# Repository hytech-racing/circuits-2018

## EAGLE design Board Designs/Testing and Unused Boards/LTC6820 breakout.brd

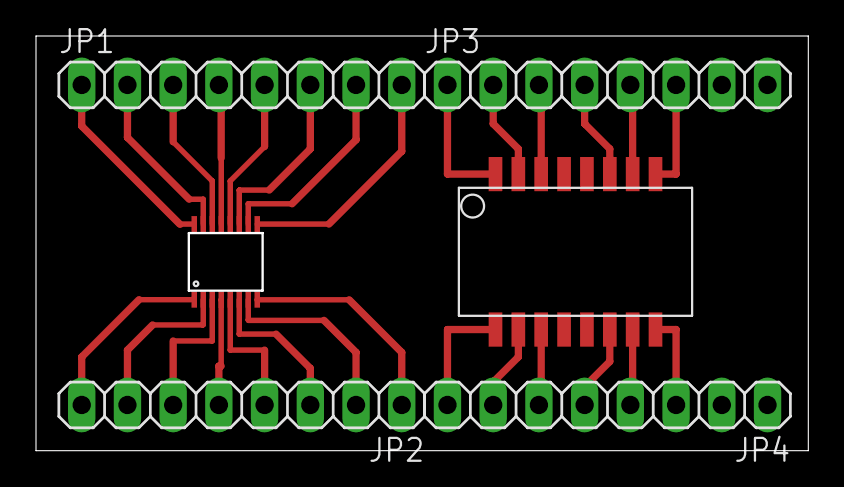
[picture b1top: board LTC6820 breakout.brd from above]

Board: 2 copper layers, 42.9 x 23.0 mm, 6 parts (0 on the bottom side), 23 nets.

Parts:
JP1, JP2, JP3, JP4: 1X08
U$1: LTC6820; MSOP-16
U$2: 749010013

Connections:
unnamed: JP2.1, U$1.8
unnamed: JP2.2, U$1.7
unnamed: JP2.3, U$1.6
unnamed: JP2.4, U$1.5
unnamed: JP2.5, U$1.4
unnamed: JP2.6, U$1.3
unnamed: JP2.7, U$1.2
unnamed: JP2.8, U$1.1
unnamed: JP1.1, U$1.16
unnamed: JP1.2, U$1.15
unnamed: JP1.3, U$1.14
unnamed: JP1.4, U$1.13
unnamed: JP1.5, U$1.12
unnamed: JP1.6, U$1.11
unnamed: JP1.7, U$1.10
unnamed: JP1.8, U$1.9
unnamed: JP4.8, U$2.16
unnamed: JP4.7, U$2.15
unnamed: JP4.6, U$2.14
unnamed: JP3.1, U$2.1
unnamed: JP3.2, U$2.2
unnamed: JP3.3, U$2.3
S$2: JP3.6, U$2.8

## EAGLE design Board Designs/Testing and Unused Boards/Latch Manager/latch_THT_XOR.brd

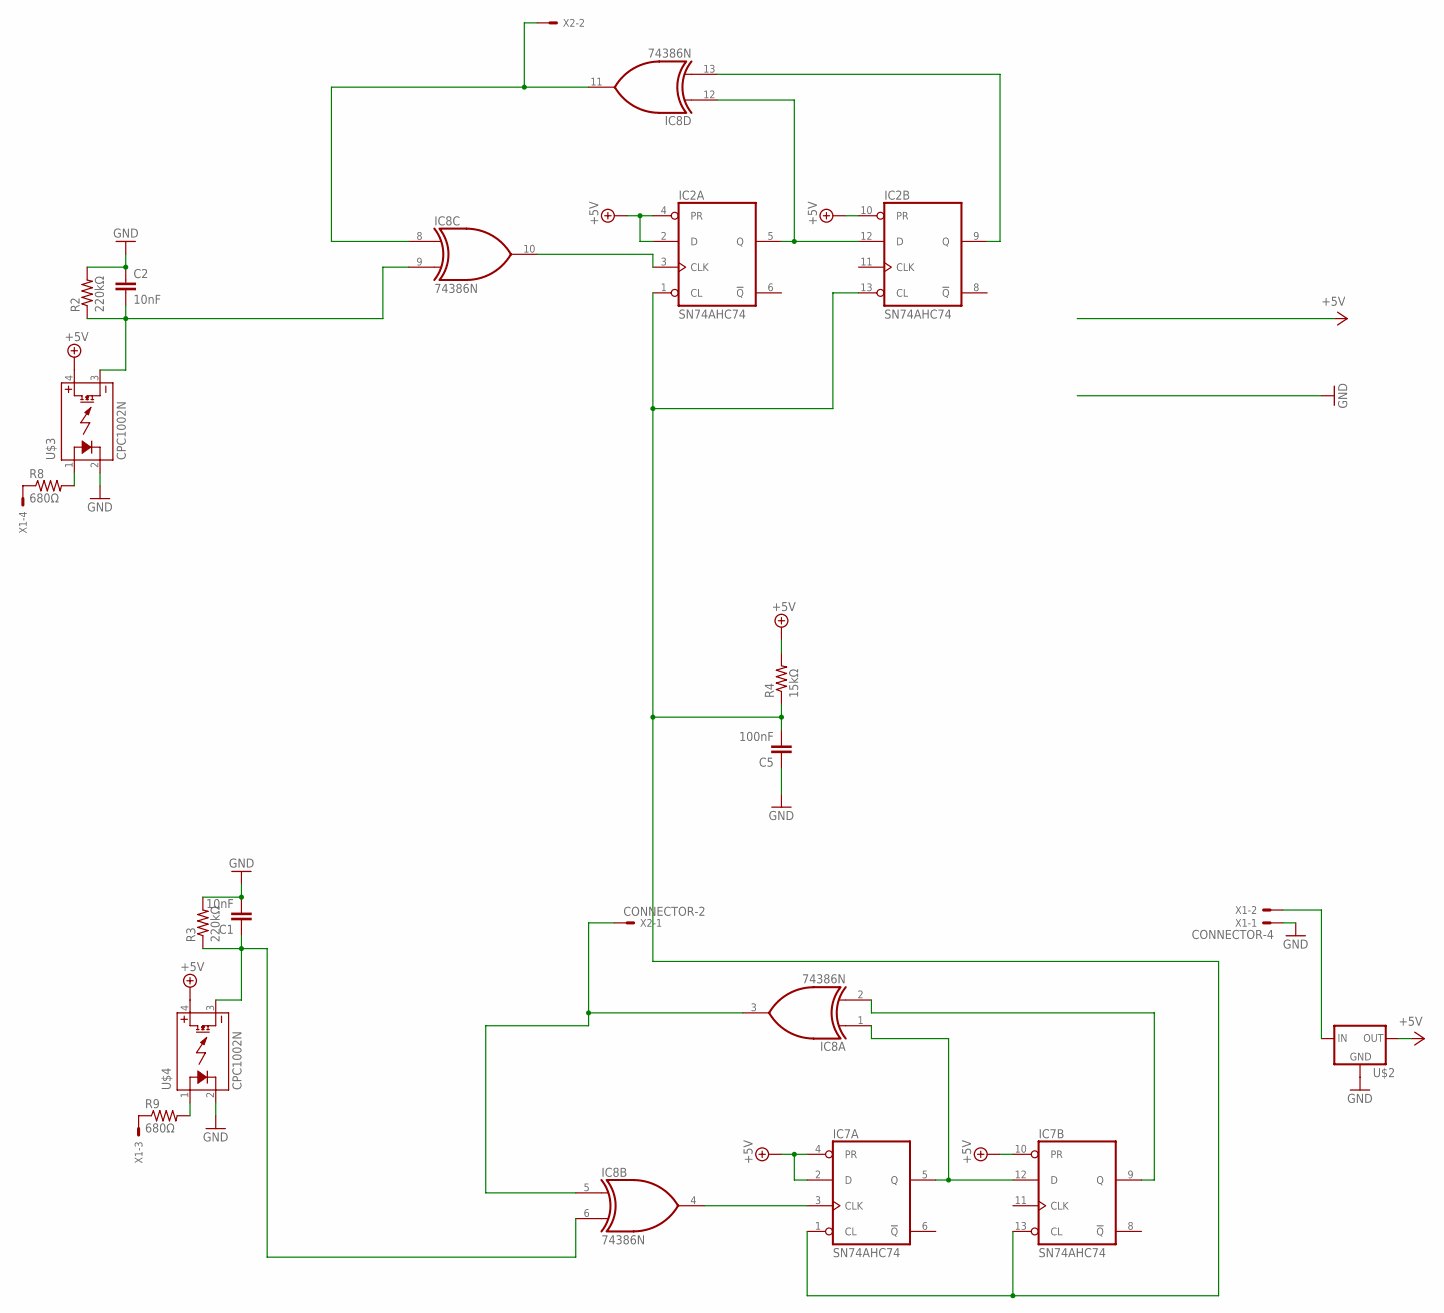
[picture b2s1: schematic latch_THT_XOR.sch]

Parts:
C1, C2: 10nF; AXIAL-5MM
C5: 100nF; AXIAL-5MM
IC2, IC7: SN74AHC74; DIL14
IC8: 74386N; DIL14
R2, R3: 220kΩ; AXIAL-0.4
R4: 15kΩ; AXIAL-0.4
R8, R9: 680Ω; AXIAL-0.4
U$2: 5VREG_LM340-NLM340T-5.0/NOPB; TO-220
U$3, U$4: CPC1002N; SOP04
X1: CONNECTOR-4; MINIFIT_5566-4
X2: CONNECTOR-2; MINIFIT_5566-2

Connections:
12V: U$2.1 (IN), X1.2
+5V: IC2.2 (D), IC2.4 (PR), IC2.10 (PR), IC2.14 (VCC), IC7.2 (D), IC7.4 (PR), IC7.10 (PR), IC7.14 (VCC), IC8.14 (VCC), R4.P$2 (2), U$2.3 (OUT), U$3.4 (DC+), U$4.4 (DC+)
BMS_IN: R9.P$2 (2), U$4.1 (CONTROL+)
GND: C1.P$2 (2), C2.P$1 (1), C5.P$1 (1), IC2.7 (GND), IC7.7 (GND), IC8.7 (GND), R2.P$2 (2), R3.P$2 (2), U$2.2 (GND), U$3.2 (CONTROL-), U$4.2 (CONTROL-), X1.1
IMD_IN: R8.P$2 (2), U$3.1 (CONTROL+)
unnamed: IC2.5 (Q), IC2.12 (D), IC8.12 (I0)
unnamed: IC2.9 (Q), IC8.13 (I1)
unnamed: C5.P$2 (2), IC2.1 (CL), IC2.13 (CL), IC7.1 (CL), IC7.13 (CL), R4.P$1 (1)
unnamed: IC8.8 (I0), IC8.11 (O), X2.2
unnamed: IC2.3 (CLK), IC8.10 (O)
unnamed: IC7.3 (CLK), IC8.4 (O)
unnamed: C1.P$1 (1), IC8.6 (I1), R3.P$1 (1), U$4.3 (DC-)
unnamed: C2.P$2 (2), IC8.9 (I1), R2.P$1 (1), U$3.3 (DC-)
unnamed: IC7.5 (Q), IC7.12 (D), IC8.1 (I0)
unnamed: IC7.9 (Q), IC8.2 (I1)
unnamed: IC8.3 (O), IC8.5 (I0), X2.1
unnamed: R8.P$1 (1), X1.4
unnamed: R9.P$1 (1), X1.3

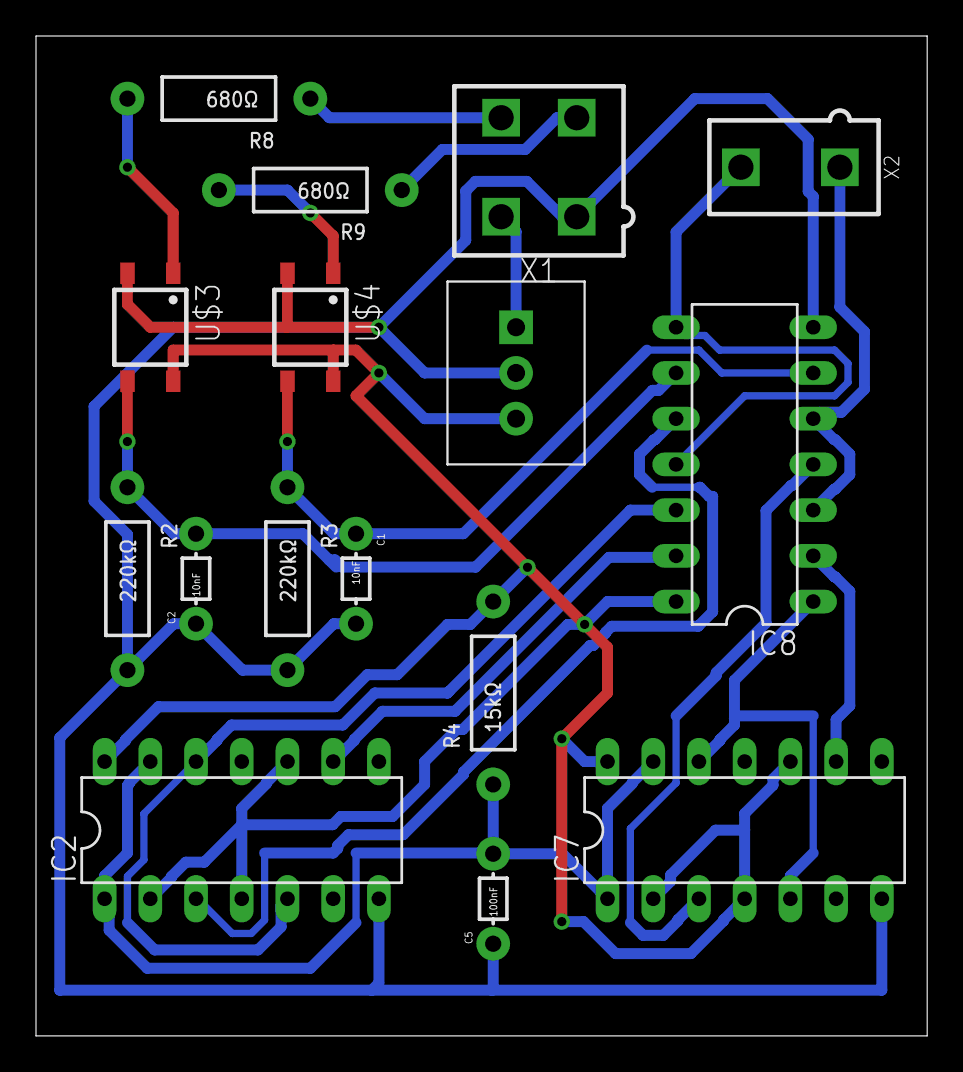
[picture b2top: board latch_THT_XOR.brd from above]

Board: 2 copper layers, 49.5 x 55.5 mm, 16 parts (0 on the bottom side), 18 nets.

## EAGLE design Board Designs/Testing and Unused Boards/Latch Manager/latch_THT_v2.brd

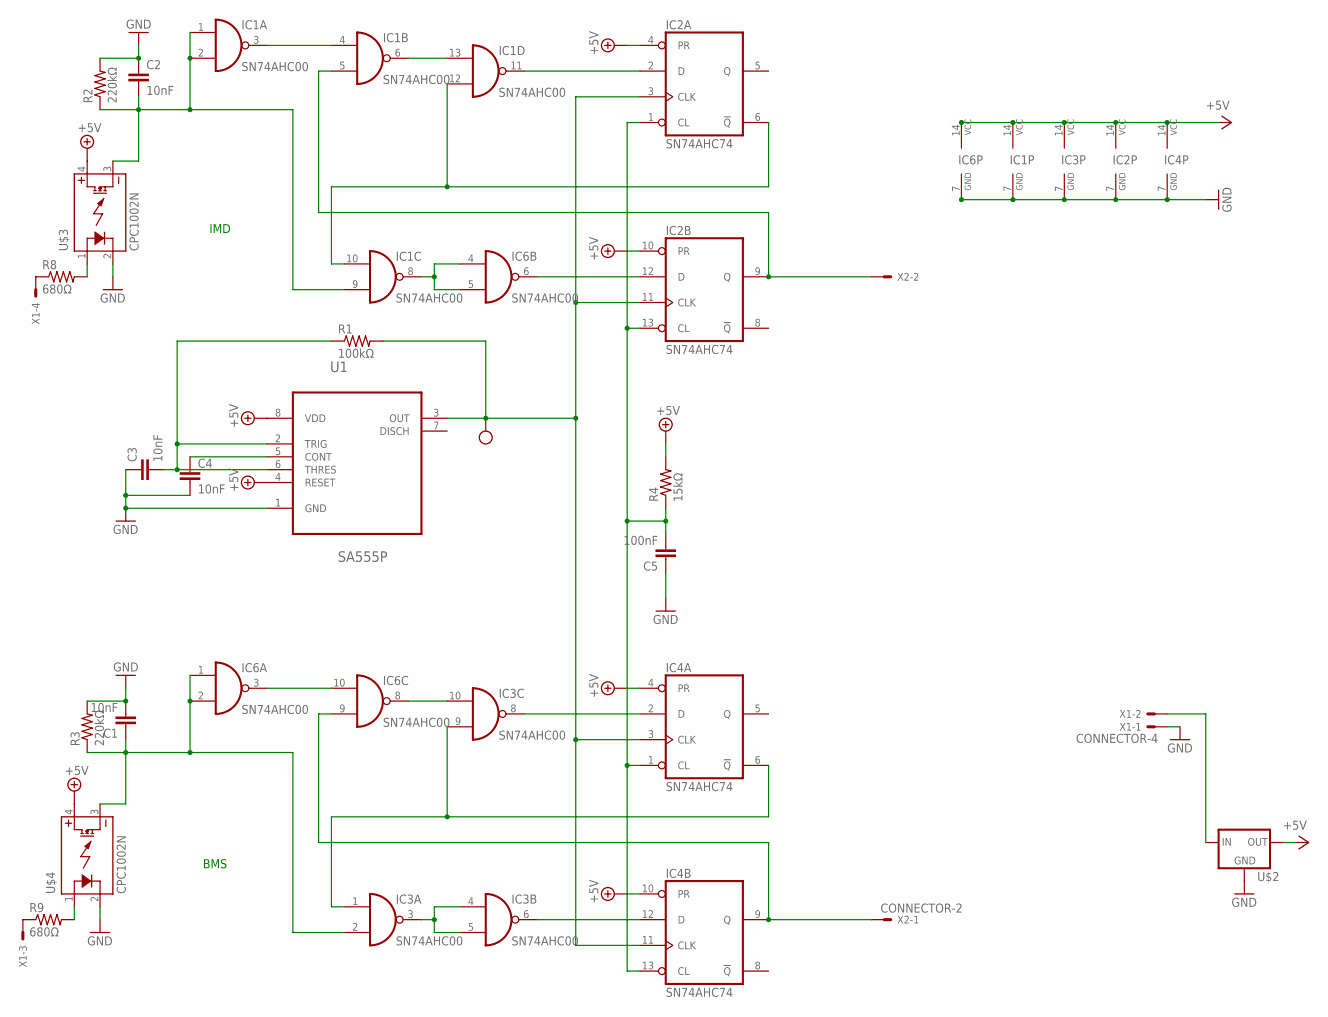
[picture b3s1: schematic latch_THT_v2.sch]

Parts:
C1, C2, C3, C4: 10nF; AXIAL-5MM
C5: 100nF; AXIAL-5MM
IC1, IC3, IC6: SN74AHC00; DIL14
IC2, IC4: SN74AHC74; DIL14
R1: 100kΩ; AXIAL-0.4
R2, R3: 220kΩ; AXIAL-0.4
R4: 15kΩ; AXIAL-0.4
R8, R9: 680Ω; AXIAL-0.4
U1: SA555P; DIP254P762X508-8
U$1: TEST_POINT
U$2: 5VREG_LM340-NLM340T-5.0/NOPB; TO-220
U$3, U$4: CPC1002N; SOP04
X1: CONNECTOR-4; MINIFIT_5566-4
X2: CONNECTOR-2; MINIFIT_5566-2

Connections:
12V: U$2.1 (IN), X1.2
+5V: IC1.14 (VCC), IC2.4 (PR), IC2.10 (PR), IC2.14 (VCC), IC3.14 (VCC), IC4.4 (PR), IC4.10 (PR), IC4.14 (VCC), IC6.14 (VCC), R4.P$2 (2), U1.4 (RESET), U1.8 (VDD), U$2.3 (OUT), U$3.4 (DC+), U$4.4 (DC+)
BMS_5V: C1.P$1 (1), IC3.2 (I1), IC6.1 (I0), IC6.2 (I1), R3.P$1 (1), U$4.3 (DC-)
BMS_IN: R9.P$2 (2), U$4.1 (CONTROL+)
BMS_OUT: IC4.9 (Q), IC6.9 (I1), X2.1
CLK: IC2.3 (CLK), IC2.11 (CLK), IC4.3 (CLK), IC4.11 (CLK), R1.P$2 (2), U1.3 (OUT), U$1.P$1
GND: C1.P$2 (2), C2.P$1 (1), C3.P$1 (1), C4.P$2 (2), C5.P$1 (1), IC1.7 (GND), IC2.7 (GND), IC3.7 (GND), IC4.7 (GND), IC6.7 (GND), R2.P$2 (2), R3.P$2 (2), U1.1 (GND), U$2.2 (GND), U$3.2 (CONTROL-), U$4.2 (CONTROL-), X1.1
IMD_5V: C2.P$2 (2), IC1.1 (I0), IC1.2 (I1), IC1.9 (I1), R2.P$1 (1), U$3.3 (DC-)
IMD_IN: R8.P$2 (2), U$3.1 (CONTROL+)
IMD_OUT: IC1.5 (I1), IC2.9 (Q), X2.2
unnamed: C5.P$2 (2), IC2.1 (CL), IC2.13 (CL), IC4.1 (CL), IC4.13 (CL), R4.P$1 (1)
unnamed: IC1.3 (O), IC1.4 (I0)
unnamed: C3.P$2 (2), R1.P$1 (1), U1.2 (TRIG), U1.6 (THRES)
unnamed: IC1.6 (O), IC1.13 (I0)
unnamed: IC1.10 (I0), IC1.12 (I1), IC2.6 (!Q)
unnamed: IC1.11 (O), IC2.2 (D)
unnamed: C4.P$1 (1), U1.5 (CONT)
unnamed: IC2.12 (D), IC6.6 (O)
unnamed: IC3.6 (O), IC4.12 (D)
unnamed: IC1.8 (O), IC6.4 (I0), IC6.5 (I1)
unnamed: IC6.3 (O), IC6.10 (I0)
unnamed: IC3.10 (I0), IC6.8 (O)
unnamed: IC3.1 (I0), IC3.9 (I1), IC4.6 (!Q)
unnamed: IC3.8 (O), IC4.2 (D)
unnamed: IC3.3 (O), IC3.4 (I0), IC3.5 (I1)
unnamed: R8.P$1 (1), X1.4
unnamed: R9.P$1 (1), X1.3

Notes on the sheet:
IMD
BMS

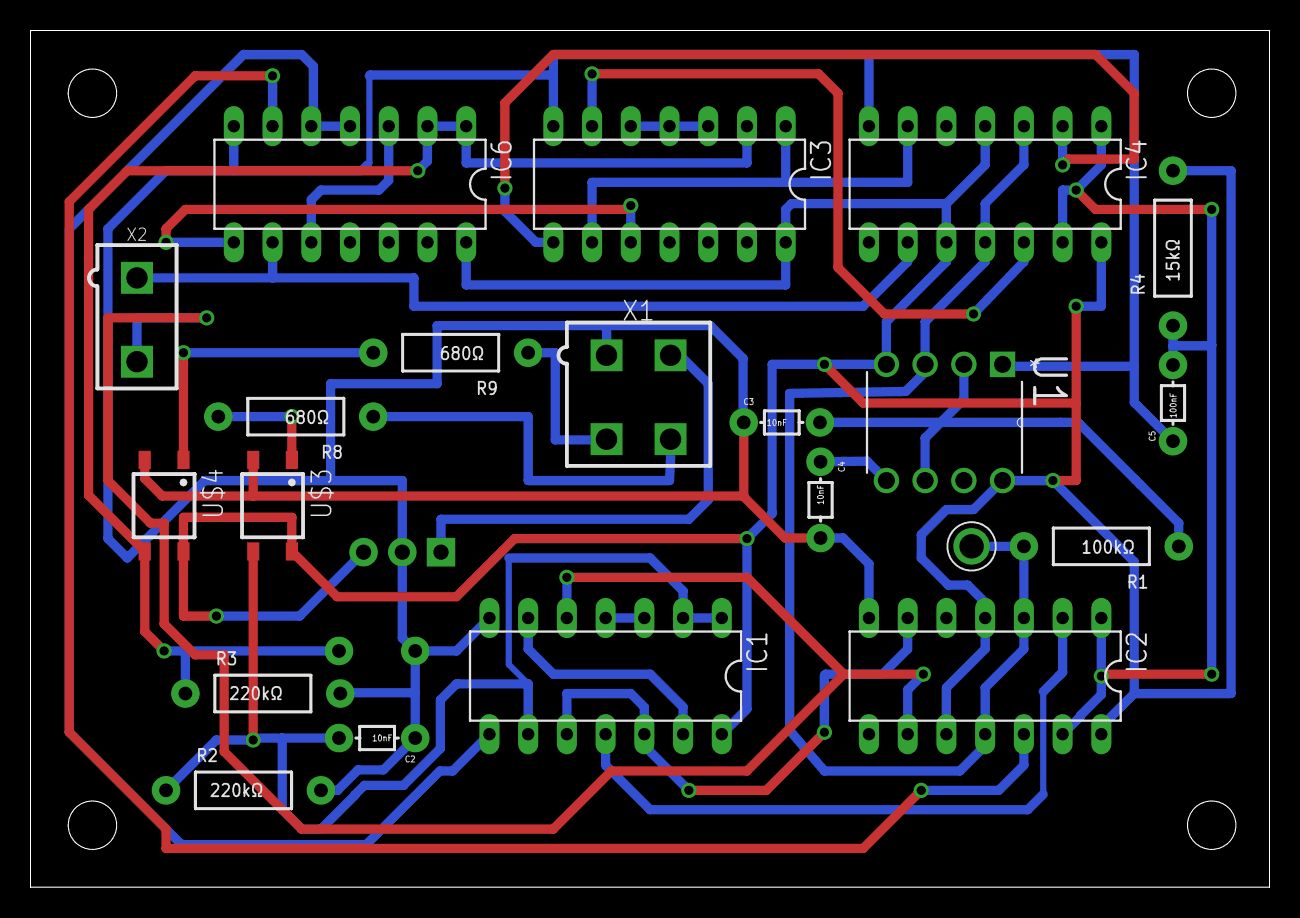
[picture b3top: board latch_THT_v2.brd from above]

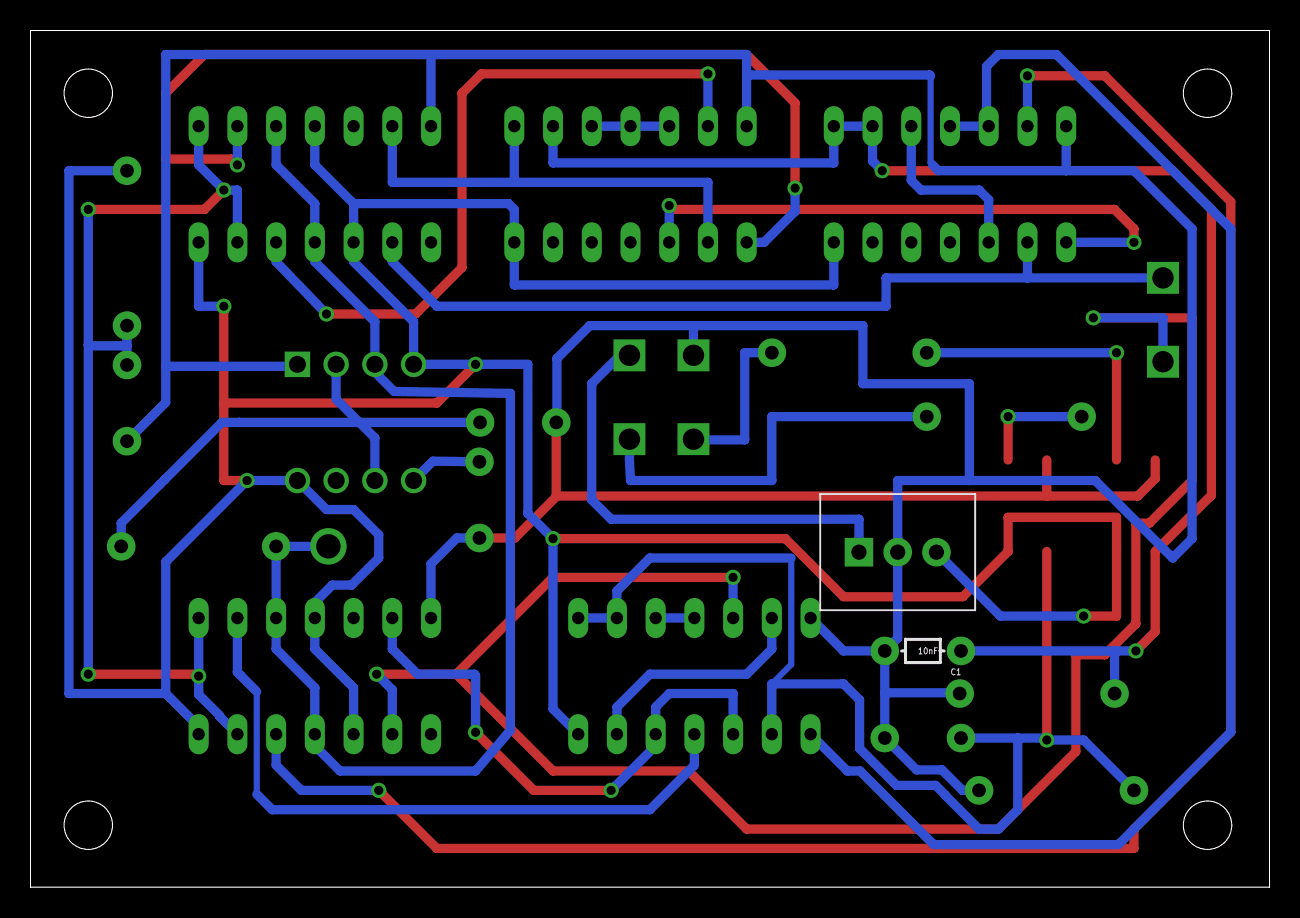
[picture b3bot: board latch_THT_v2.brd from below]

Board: 2 copper layers, 81.3 x 56.2 mm, 23 parts (2 on the bottom side), 27 nets.

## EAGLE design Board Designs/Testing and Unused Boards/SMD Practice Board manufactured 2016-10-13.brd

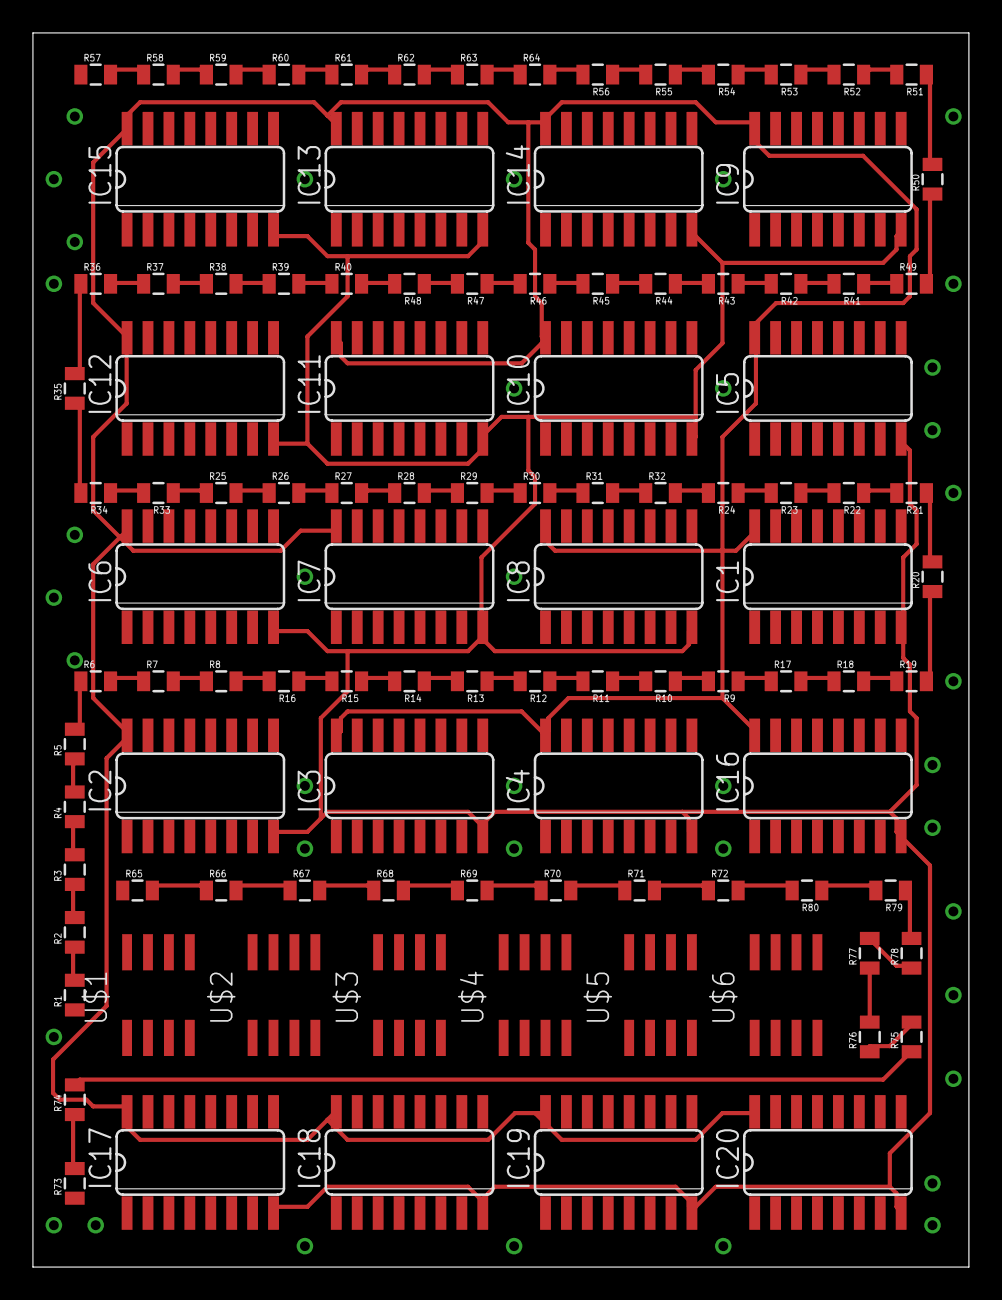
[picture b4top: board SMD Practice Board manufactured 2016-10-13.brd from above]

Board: 2 copper layers, 56.8 x 74.9 mm, 106 parts (0 on the bottom side), 80 nets.

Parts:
IC1, IC2, IC3, IC4, IC5, IC6, IC7, IC8, IC9, IC10, IC11, IC12, IC13, IC14, IC15, IC16, IC17, IC18, IC19, IC20: 74LS258D; SO16
R1, R2, R3, R4, R5, R6, R7, R8, R9, R10, R11, R12, R13, R14, R15, R16, R17, R18, R19, R20, R21, R22, R23, R24, R25, R26, R27, R28, R29, R30, R31, R32, R33, R34, R35, R36, R37, R38, R39, R40, R41, R42, R43, R44, R45, R46, R47, R48, R49, R50, R51, R52, R53, R54, R55, R56, R57, R58, R59, R60, R61, R62, R63, R64, R65, R66, R67, R68, R69, R70, R71, R72, R73, R74, R75, R76, R77, R78, R79, R80: 0805
U$1, U$2, U$3, U$4, U$5, U$6: MCP2551; SOIC-08

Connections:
GND: IC1.8, IC2.8, IC3.8, IC4.8, IC5.8, IC6.8, IC7.8, IC8.8, IC9.8, IC10.8, IC11.8, IC12.8, IC13.8, IC14.8, IC15.8, IC16.8, IC17.8, IC18.8, IC19.8, IC20.8
unnamed: R1.2, R2.1
unnamed: R2.2, R3.1
unnamed: R3.2, R4.1
unnamed: R5.2, R6.1
unnamed: R6.2, R7.1
unnamed: R7.2, R8.1
unnamed: R4.2, R5.1
unnamed: R9.2, R10.1
unnamed: R10.2, R11.1
unnamed: R11.2, R12.1
unnamed: R13.2, R14.1
unnamed: R14.2, R15.1
unnamed: R15.2, R16.1
unnamed: R12.2, R13.1
unnamed: R8.2, R16.2
unnamed: R17.2, R18.1
unnamed: R18.2, R19.1
unnamed: R19.2, R20.1
unnamed: R21.2, R22.1
unnamed: R22.2, R23.1
unnamed: R23.2, R24.1
unnamed: R20.2, R21.1
unnamed: R25.2, R26.1
unnamed: R26.2, R27.1
unnamed: R27.2, R28.1
unnamed: R29.2, R30.1
unnamed: R30.2, R31.1
unnamed: R31.2, R32.1
unnamed: R28.2, R29.1
unnamed: R24.2, R32.2
unnamed: R9.1, R17.1
unnamed: R33.2, R34.1
unnamed: R34.2, R35.1
unnamed: R35.2, R36.1
unnamed: R37.2, R38.1
unnamed: R38.2, R39.1
unnamed: R39.2, R40.1
unnamed: R36.2, R37.1
unnamed: R41.2, R42.1
unnamed: R42.2, R43.1
unnamed: R43.2, R44.1
unnamed: R45.2, R46.1
unnamed: R46.2, R47.1
unnamed: R47.2, R48.1
unnamed: R44.2, R45.1
unnamed: R40.2, R48.2
unnamed: R49.2, R50.1
unnamed: R50.2, R51.1
unnamed: R51.2, R52.1
unnamed: R53.2, R54.1
unnamed: R54.2, R55.1
unnamed: R55.2, R56.1
unnamed: R52.2, R53.1
unnamed: R57.2, R58.1
unnamed: R58.2, R59.1
unnamed: R59.2, R60.1
unnamed: R61.2, R62.1
unnamed: R62.2, R63.1
unnamed: R63.2, R64.1
unnamed: R60.2, R61.1
unnamed: R56.2, R64.2
unnamed: R41.1, R49.1
unnamed: R25.1, R33.1
unnamed: R65.2, R66.1
unnamed: R66.2, R67.1
unnamed: R67.2, R68.1
unnamed: R69.2, R70.1
unnamed: R70.2, R71.1
unnamed: R71.2, R72.1
unnamed: R68.2, R69.1
unnamed: R73.2, R74.1
unnamed: R74.2, R75.1
unnamed: R75.2, R76.1
unnamed: R77.2, R78.1
unnamed: R78.2, R79.1
unnamed: R79.2, R80.1
unnamed: R76.2, R77.1
unnamed: R72.2, R80.2
VCC: IC1.16, IC2.16, IC3.16, IC4.16, IC5.16, IC6.16, IC7.16, IC8.16, IC9.16, IC10.16, IC11.16, IC12.16, IC13.16, IC14.16, IC15.16, IC16.16, IC17.16, IC18.16, IC19.16, IC20.16

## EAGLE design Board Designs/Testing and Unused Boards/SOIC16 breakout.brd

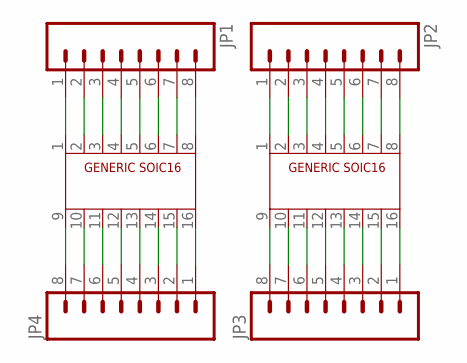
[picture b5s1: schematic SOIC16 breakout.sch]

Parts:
JP1, JP2, JP3, JP4: M08; 1X08
U$1, U$2: SOIC16; SOIC-16

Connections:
unnamed: JP1.1, U$1.1
unnamed: JP1.2, U$1.2
unnamed: JP1.3, U$1.3
unnamed: JP1.4, U$1.4
unnamed: JP1.5, U$1.5
unnamed: JP1.6, U$1.6
unnamed: JP1.7, U$1.7
unnamed: JP1.8, U$1.8
unnamed: JP2.1, U$2.1
unnamed: JP2.2, U$2.2
unnamed: JP2.3, U$2.3
unnamed: JP2.4, U$2.4
unnamed: JP2.5, U$2.5
unnamed: JP2.6, U$2.6
unnamed: JP2.7, U$2.7
unnamed: JP2.8, U$2.8
unnamed: JP3.1, U$2.16
unnamed: JP3.2, U$2.15
unnamed: JP3.3, U$2.14
unnamed: JP3.4, U$2.13
unnamed: JP3.5, U$2.12
unnamed: JP3.6, U$2.11
unnamed: JP3.7, U$2.10
unnamed: JP3.8, U$2.9
unnamed: JP4.1, U$1.16
unnamed: JP4.2, U$1.15
unnamed: JP4.3, U$1.14
unnamed: JP4.4, U$1.13
unnamed: JP4.5, U$1.12
unnamed: JP4.6, U$1.11
unnamed: JP4.7, U$1.10
unnamed: JP4.8, U$1.9

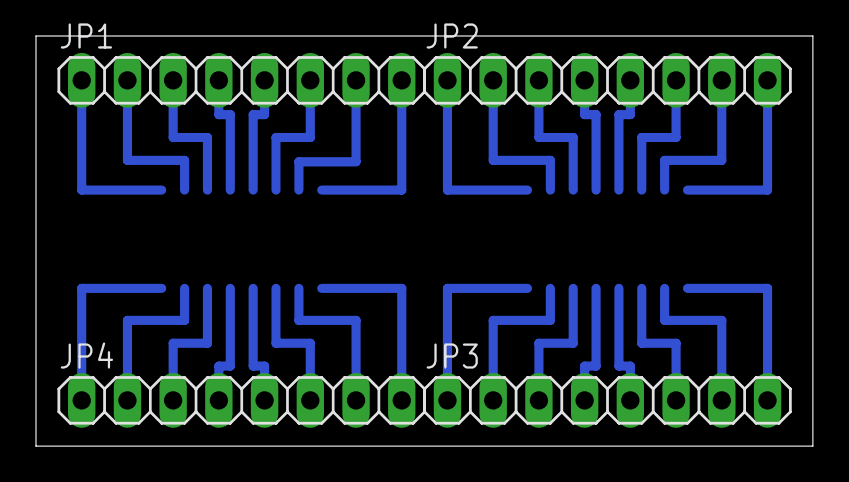
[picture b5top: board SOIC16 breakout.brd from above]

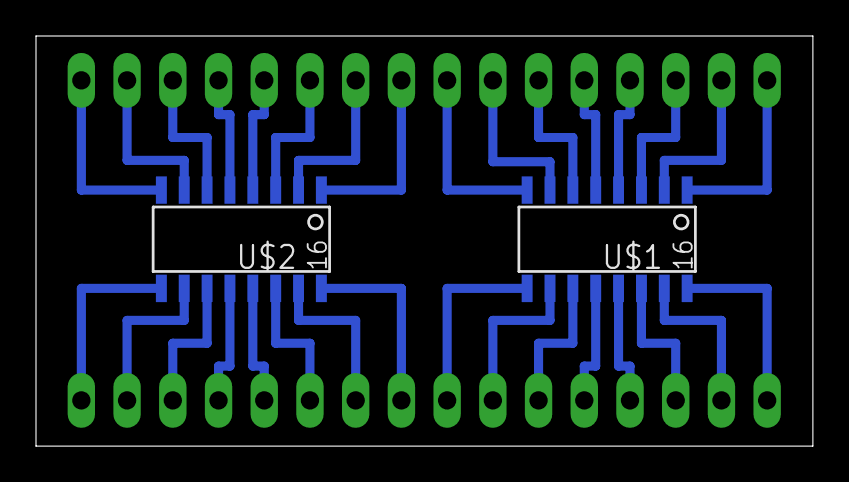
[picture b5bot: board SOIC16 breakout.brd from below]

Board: 2 copper layers, 43.2 x 22.8 mm, 6 parts (2 on the bottom side), 32 nets.

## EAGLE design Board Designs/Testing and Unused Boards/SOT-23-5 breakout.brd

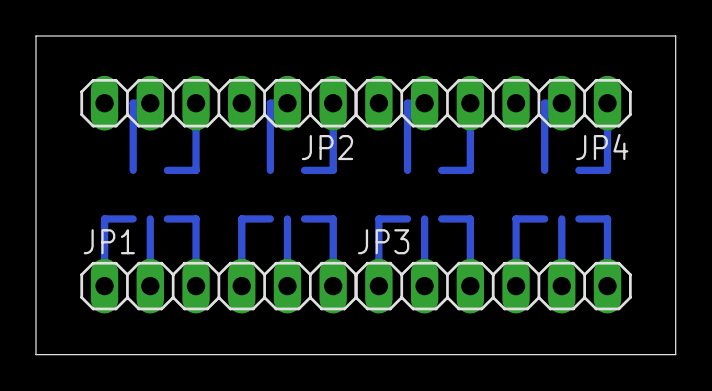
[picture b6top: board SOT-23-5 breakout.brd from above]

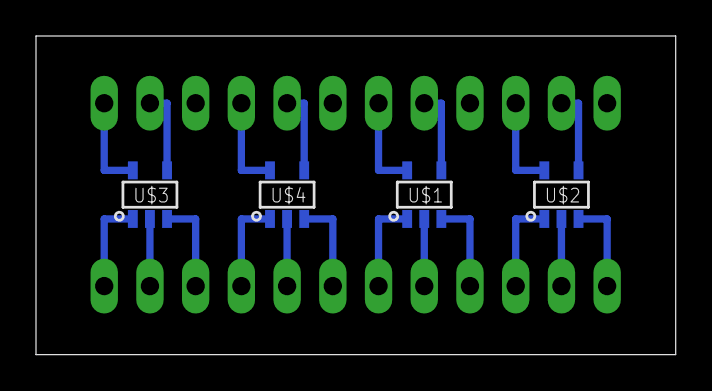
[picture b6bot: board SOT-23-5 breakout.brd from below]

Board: 2 copper layers, 35.5 x 17.7 mm, 8 parts (4 on the bottom side), 20 nets.

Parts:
JP1, JP2, JP3, JP4: 1X06
U$1, U$3: SN74LVC1G06; SOT-23-5
U$2, U$4: SN74LVC1G07; SOT-23-5

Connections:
unnamed: JP2.1, U$1.5
unnamed: JP2.2, U$1.4
unnamed: JP2.4, U$2.5
unnamed: JP2.5, U$2.4
unnamed: JP1.6, U$1.1
unnamed: JP1.5, U$1.2
unnamed: JP1.4, U$1.3
unnamed: JP1.3, U$2.1
unnamed: JP1.2, U$2.2
unnamed: JP1.1, U$2.3
unnamed: JP4.1, U$3.5
unnamed: JP4.2, U$3.4
unnamed: JP4.4, U$4.5
unnamed: JP4.5, U$4.4
unnamed: JP3.6, U$3.1
unnamed: JP3.5, U$3.2
unnamed: JP3.4, U$3.3
unnamed: JP3.3, U$4.1
unnamed: JP3.2, U$4.2
unnamed: JP3.1, U$4.3

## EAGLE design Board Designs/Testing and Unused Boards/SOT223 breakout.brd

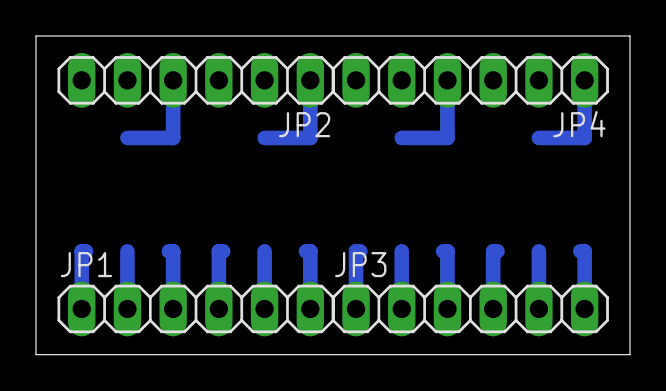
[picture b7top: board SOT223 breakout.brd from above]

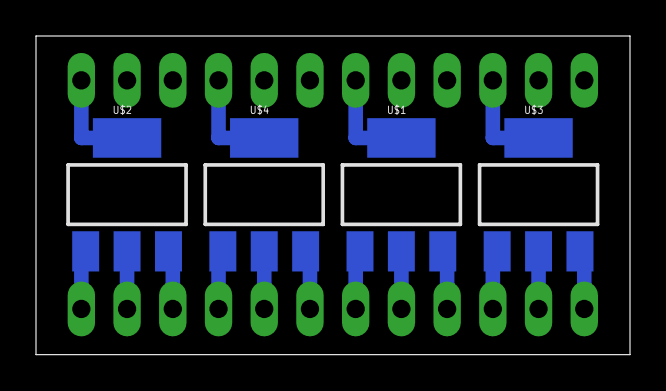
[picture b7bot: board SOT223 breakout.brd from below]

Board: 2 copper layers, 33.0 x 17.7 mm, 8 parts (4 on the bottom side), 16 nets.

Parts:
JP1, JP2, JP3, JP4: 1X06
U$1, U$2, U$3, U$4: SOT223

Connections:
unnamed: JP2.1, U$1.4
unnamed: JP1.6, U$1.1
unnamed: JP1.5, U$1.2
unnamed: JP1.4, U$1.3
unnamed: JP1.3, U$3.1
unnamed: JP1.2, U$3.2
unnamed: JP1.1, U$3.3
unnamed: JP2.4, U$3.4
unnamed: JP4.1, U$2.4
unnamed: JP4.4, U$4.4
unnamed: JP3.6, U$2.1
unnamed: JP3.5, U$2.2
unnamed: JP3.4, U$2.3
unnamed: JP3.3, U$4.1
unnamed: JP3.2, U$4.2
unnamed: JP3.1, U$4.3

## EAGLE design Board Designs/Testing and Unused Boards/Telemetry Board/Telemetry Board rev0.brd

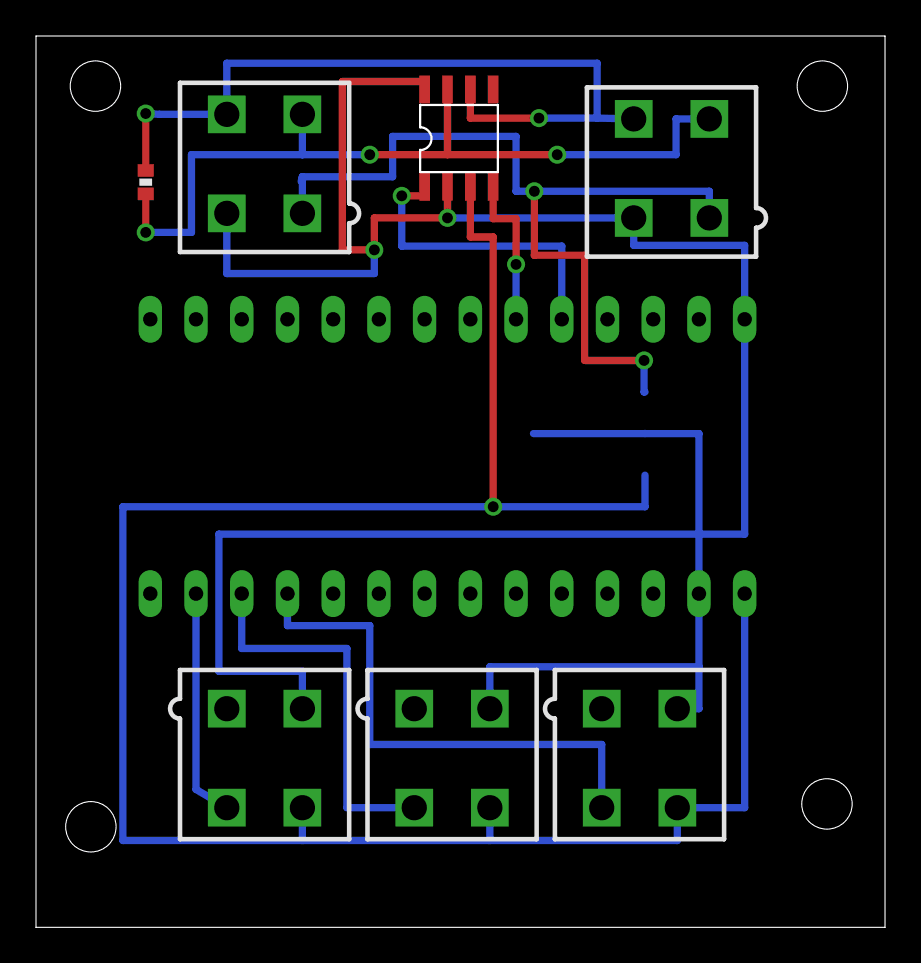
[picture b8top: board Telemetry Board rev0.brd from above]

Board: 2 copper layers, 47.2 x 49.5 mm, 9 parts (1 on the bottom side), 10 nets.

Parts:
120: 0402-RES
ADAD: MINIFIT_5566-4
U$1: TEENSY_3.2_SIMPLE
U$2: MCP2551SOIC; SOIC08
U$3: SOT223
X1: Suspension Sensor; MINIFIT_5566-4
X2: Wheel Sensor; MINIFIT_5566-4
X3: Tire Temperature Sensor; MINIFIT_5566-4
X5: MINIFIT_5566-4

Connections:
unnamed: ADAD.1, U$3.1, X5.1
unnamed: 120.2, ADAD.3, U$2.7, X5.3
unnamed: 120.1, ADAD.4, U$2.6, X5.4
unnamed: ADAD.2, U$1.AGND, U$1.GND, U$2.2, U$2.8, U$3.2, U$3.4, X1.2, X2.2, X3.2, X5.2
unnamed: U$1.D3(CANTX), U$2.1
unnamed: U$1.D4(CANRX), U$2.4
unnamed: U$1.A1, X3.3
unnamed: U$1.VIN, U$2.3, U$3.3, X1.4, X2.4, X3.4
unnamed: U$1.A0, X2.3
unnamed: U$1.A2, X1.3
